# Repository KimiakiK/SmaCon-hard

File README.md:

# SmaCon-hard

# Features
- 

# Major Components
- STM32U575CIU6Q
Arm Cortex-M33 160MHz ROM 2MB RAM 786KB UFQFPN-48
- LCD
2.8inch 240x320 IPS ST7789 Touch GT911
- YMF825
FM音源
- 振動モータ
LD14-002

# Photos

# Parts List
- [STM32U575CIU6Q](https://mou.sr/46YhdRg)
- LCD (AliExpress)
- FM音源 YMF825 (AliExpress)
- [スピーカー](https://akizukidenshi.com/catalog/g/gP-12495/)
- [水晶振動子 12.228MHz](https://www.marutsu.co.jp/pc/i/1542722/)
- [3.5mmステレオミニジャック](https://www.marutsu.co.jp/pc/i/590750/)
- [EEPROM 1KB 25LC080C-E/MS](https://mou.sr/3XQXcYr)
- [振動モータ LD14-002](https://akizukidenshi.com/catalog/g/gP-06838/)
- [モータドライバ BD6211F](https://akizukidenshi.com/catalog/g/gI-05087/)
- [USB Type-Cコネクタ 5077CR-16SMC2-BK-TR](https://akizukidenshi.com/catalog/g/gC-14356/)
- [アナログジョイスティック JT8P-3.2T-B10K-1-16Y](https://akizukidenshi.com/catalog/g/gP-04048/)
- [タクトスイッチ(赤)](https://akizukidenshi.com/catalog/g/gP-03646/)
- [タクトスイッチ(黄)](https://akizukidenshi.com/catalog/g/gP-03650/)
- [タクトスイッチ(緑)](https://akizukidenshi.com/catalog/g/gP-03651/)
- [タクトスイッチ(青)](https://akizukidenshi.com/catalog/g/gP-03649/)
- [レバースイッチ TMHU27](https://akizukidenshi.com/catalog/g/gP-08071/)
- [リセットIC BD45285G 2.5V 50ms](https://www.marutsu.co.jp/pc/i/16146424/)
- [レギュレータ NJM2884U1-33 3.3V 500mA](https://akizukidenshi.com/catalog/g/gI-10673/)
- [ESD保護デバイス LXES11DAA2-137](https://akizukidenshi.com/catalog/g/gP-13816/)
- [フェライトビーズ BLM18PG600SH1](https://akizukidenshi.com/catalog/g/gP-04442/)
- [リセッタブルヒューズ 0.5A MF-NSMF050](https://akizukidenshi.com/catalog/g/gP-15300/)
- [NchパワーMOSFET AO3400A](https://akizukidenshi.com/catalog/g/gI-14653/)
- [FFCコネクタ 18pin 0.5mm](https://www.marutsu.co.jp/pc/i/2572902/)
- [FFCコネクタ 6pin 0.5mm](https://www.marutsu.co.jp/pc/i/2572910/)

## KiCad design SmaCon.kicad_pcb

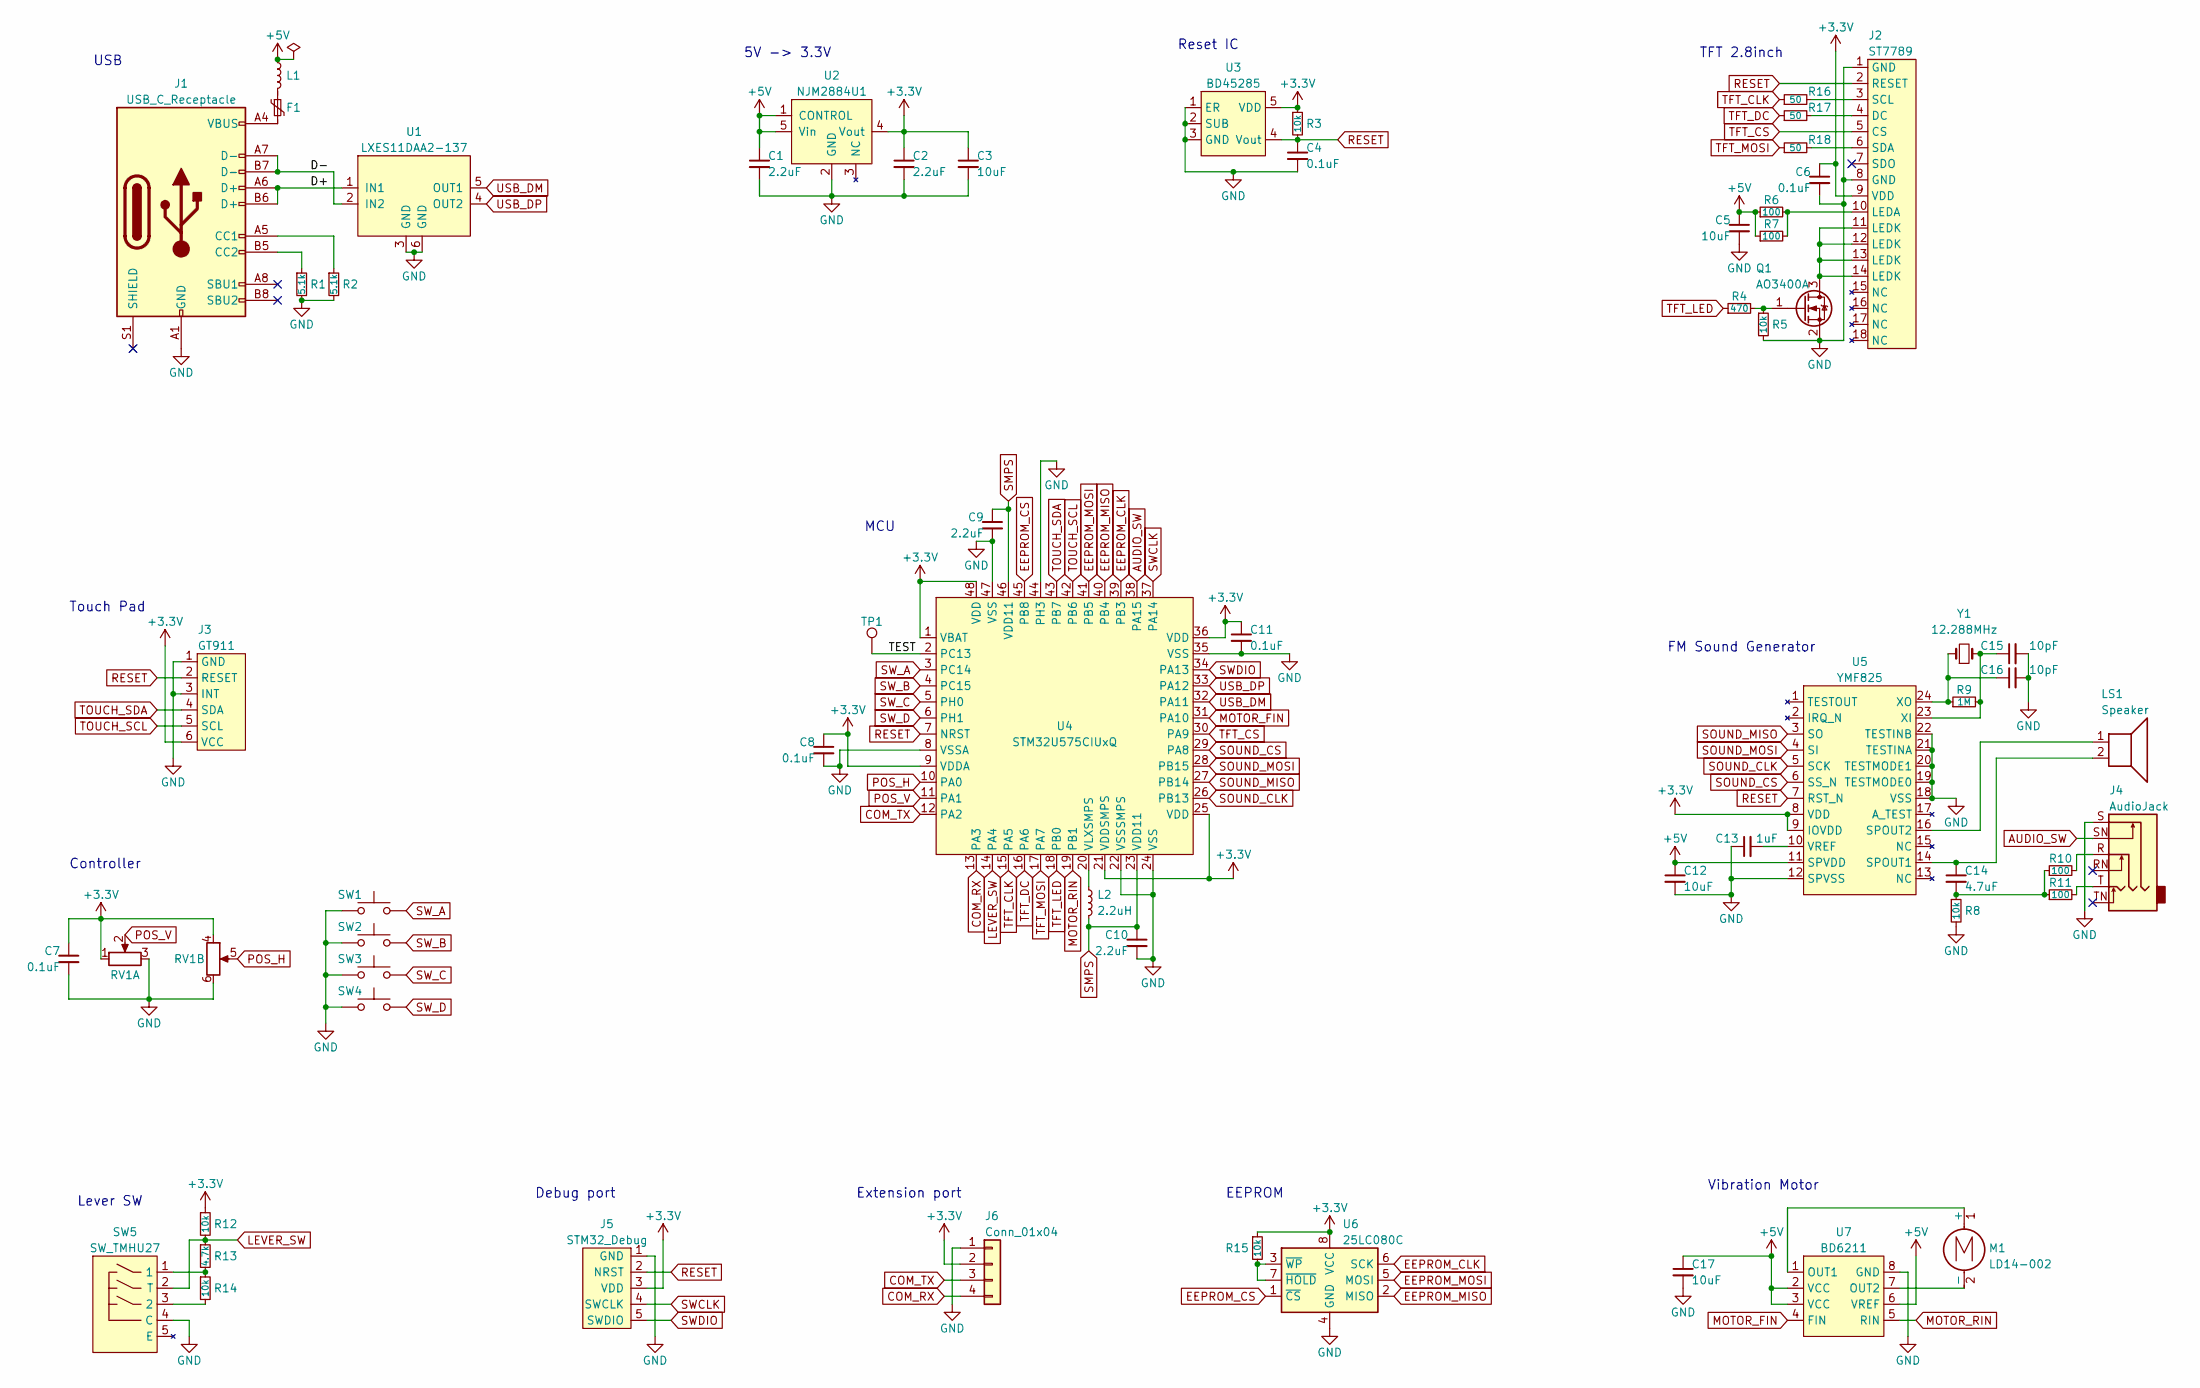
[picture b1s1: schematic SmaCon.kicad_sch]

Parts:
C1, C2, C9, C10: 2.2uF; 1005Metric
C3, C5, C12, C17: 10uF; 1608Metric
C4, C6, C7, C8, C11: 0.1uF; 1005Metric
C13: 1uF; 1005Metric
C14: 4.7uF; 1608Metric
C15, C16: 10pF; 1005Metric
F1: Polyfuse; 3216Metric
J1: USB_C_Receptacle; USB Type-C 5077CR-16SMC2-BK-TR
J2: ST7789; Hirose_FH12-18S-0.5SH_1x18-1MP_P0.50mm_Horizontal
J3: GT911; Hirose_FH12-6S-0.5SH_1x06-1MP_P0.50mm_Horizontal
J4: AudioJack; PJ-3420
J5: STM32_Debug; STM32_Debug_5pin
J6: Conn_01x04; PinHeader_1x04_P2.54mm_Horizontal
L1: L; 1608Metric
L2: 2.2uH; 2012Metric
LS1: Speaker; micro_speaker
M1: LD14-002
Q1: AO3400A; SOT-23
R1, R2: 5.1k; 1005Metric
R3, R5, R8, R12, R14, R15: 10k; 1005Metric
R4: 470; 1005Metric
R6, R7, R10, R11: 100; 2012Metric
R9: 1M; 1005Metric
R13: 4.7k; 1005Metric
R16, R17, R18: 50; 1005Metric
RV1: Potentiometer_Dual; JT8P-3.2T-B10K-1-16Y
SW1, SW2, SW3, SW4: SW_Push; tact_switch
SW5: SW_TMHU27
TP1: TestPoint; TestPoint_THTPad_D1.2mm_Drill0.8mm
U1: LXES11DAA2-137; LXES11D
U2: NJM2884U1; SOT-89-5
U3: BD45285; SOT-23-5
U4: STM32U575CIUxQ; QFN-48-1EP_7x7mm_P0.5mm_EP5.3x5.3mm
U5: YMF825; SSOP-24_5.3x8.2mm_P0.65mm
U6: 25LC080C; MSOP-8_3x3mm_P0.65mm
U7: BD6211; SOP-8_4.4x5.0mm_P1.27mm
Y1: 12.288MHz; Crystal_SMD_TXC_AX_8045-2Pin_8.0x4.5mm

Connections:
+3.3V: C2.1, C3.1, C6.1, C7.1, C8.1, C11.1, J2.9 (VDD), J3.6 (VCC), J5.3 (VDD), J6.2, R3.1, R12.1, R15.1, RV1.1, RV1.4, U2.4 (Vout), U3.5 (VDD), U4.1 (VBAT), U4.9 (VDDA), U4.21 (VDDSMPS), U4.25 (VDD), U4.36 (VDD), U4.48 (VDD), U5.8 (VDD), U5.9 (IOVDD), U6.8 (VCC)
+5V: C1.1, C5.1, C12.1, C17.1, L1.1, R6.1, R7.1, U2.1 (CONTROL), U2.5 (Vin), U5.11 (SPVDD), U7.2 (VCC), U7.3 (VCC), U7.6 (VREF)
/D+: J1.A6 (D+), J1.B6 (D+), U1.1 (IN1)
/D-: J1.A7 (D-), J1.B7 (D-), U1.2 (IN2)
/TEST: TP1.1, U4.2 (PC13)
AUDIO_SW: J4.SN, U4.38 (PA15)
COM_RX: J6.4, U4.13 (PA3)
COM_TX: J6.3, U4.12 (PA2)
EEPROM_CLK: U4.39 (PB3), U6.6 (SCK)
EEPROM_CS: U4.45 (PB8), U6.1 (~CS)
EEPROM_MISO: U4.40 (PB4), U6.2 (MISO)
EEPROM_MOSI: U4.41 (PB5), U6.5 (MOSI)
GND: C1.2, C2.2, C3.2, C4.2, C5.2, C6.2, C7.2, C8.2, C9.2, C10.2, C11.2, C12.2, C13.1, C15.2, C16.2, C17.2, J1.A1 (GND), J1.A12 (GND), J1.B1 (GND), J1.B12 (GND), J2.1 (GND), J2.8 (GND), J3.1 (GND), J3.3 (INT), J4.S, J5.1 (GND), J6.1, Q1.2 (S), R1.2, R2.2, R5.2, R8.2, RV1.3, RV1.6, SW1.1, SW2.1, SW3.1, SW4.1, SW5.4 (C), U1.3 (GND), U1.6 (GND), U2.2 (GND), U3.1 (ER), U3.2 (SUB), U3.3 (GND), U4.8 (VSSA), U4.22 (VSSSMPS), U4.24 (VSS), U4.35 (VSS), U4.44 (PH3), U4.47 (VSS), U5.12 (SPVSS), U5.18 (VSS), U5.19 (TESTMODE0), U5.20 (TESTMODE1), U5.21 (TESTINA), U5.22 (TESTINB), U6.4 (GND), U7.8 (GND)
LEVER_SW: R12.2, R13.1, SW5.2 (T), U4.14 (PA4)
MOTOR_FIN: U4.31 (PA10), U7.4 (FIN)
MOTOR_RIN: U4.19 (PB1), U7.5 (RIN)
unnamed: C14.2, R8.1, R10.1, R11.1
unnamed: F1.1, L1.2
unnamed: F1.2, J1.A4 (VBUS), J1.A9 (VBUS), J1.B4 (VBUS), J1.B9 (VBUS)
unnamed: J1.A5 (CC1), R2.1
unnamed: J1.B5 (CC2), R1.1
unnamed: J2.4 (DC), R17.2
unnamed: J2.10 (LEDA), R6.2, R7.2
unnamed: J2.3 (SCL), R16.2
unnamed: J2.6 (SDA), R18.2
unnamed: J4.R, R10.2
unnamed: J4.T, R11.2
unnamed: M1.1 (+), U7.1 (OUT1)
unnamed: M1.2 (-), U7.7 (OUT2)
unnamed: J2.11 (LEDK), J2.12 (LEDK), J2.13 (LEDK), J2.14 (LEDK), Q1.3 (D)
unnamed: Q1.1 (G), R4.2, R5.1
unnamed: R13.2, R14.1, SW5.1
unnamed: R14.2, SW5.3 (2)
unnamed: L2.1, U4.20 (VLXSMPS)
unnamed: C14.1, LS1.2, U5.14 (SPOUT1)
unnamed: LS1.1, U5.16 (SPOUT2)
unnamed: C13.2, U5.10 (VREF)
unnamed: C15.1, R9.2, U5.23 (XI), Y1.2
unnamed: C16.1, R9.1, U5.24 (XO), Y1.1
unnamed: R15.2, U6.3 (~WP), U6.7 (~HOLD)
POS_H: RV1.5, U4.10 (PA0)
POS_V: RV1.2, U4.11 (PA1)
RESET: C4.1, J2.2 (RESET), J3.2 (RESET), J5.2 (NRST), R3.2, U3.4 (Vout), U4.7 (NRST), U5.7 (RST_N)
SMPS: C9.1, C10.1, L2.2, U4.23 (VDD11), U4.46 (VDD11)
SOUND_CLK: U4.26 (PB13), U5.5 (SCK)
SOUND_CS: U4.29 (PA8), U5.6 (SS_N)
SOUND_MISO: U4.27 (PB14), U5.3 (SO)
SOUND_MOSI: U4.28 (PB15), U5.4 (SI)
SWCLK: J5.4 (SWCLK), U4.37 (PA14)
SWDIO: J5.5 (SWDIO), U4.34 (PA13)
SW_A: SW1.2, U4.3 (PC14)
SW_B: SW2.2, U4.4 (PC15)
SW_C: SW3.2, U4.5 (PH0)
SW_D: SW4.2, U4.6 (PH1)
TFT_CLK: R16.1, U4.15 (PA5)
TFT_CS: J2.5 (CS), U4.30 (PA9)
TFT_DC: R17.1, U4.16 (PA6)
TFT_LED: R4.1, U4.18 (PB0)
TFT_MOSI: R18.1, U4.17 (PA7)
TOUCH_SCL: J3.5 (SCL), U4.42 (PB6)
TOUCH_SDA: J3.4 (SDA), U4.43 (PB7)
USB_DM: U1.5 (OUT1), U4.32 (PA11)
USB_DP: U1.4 (OUT2), U4.33 (PA12)

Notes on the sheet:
Controller
Reset IC
Extension port
Vibration Motor
USB
EEPROM
Touch Pad
Lever SW
FM Sound Generator
Debug port
TFT 2.8inch
5V -> 3.3V
MCU

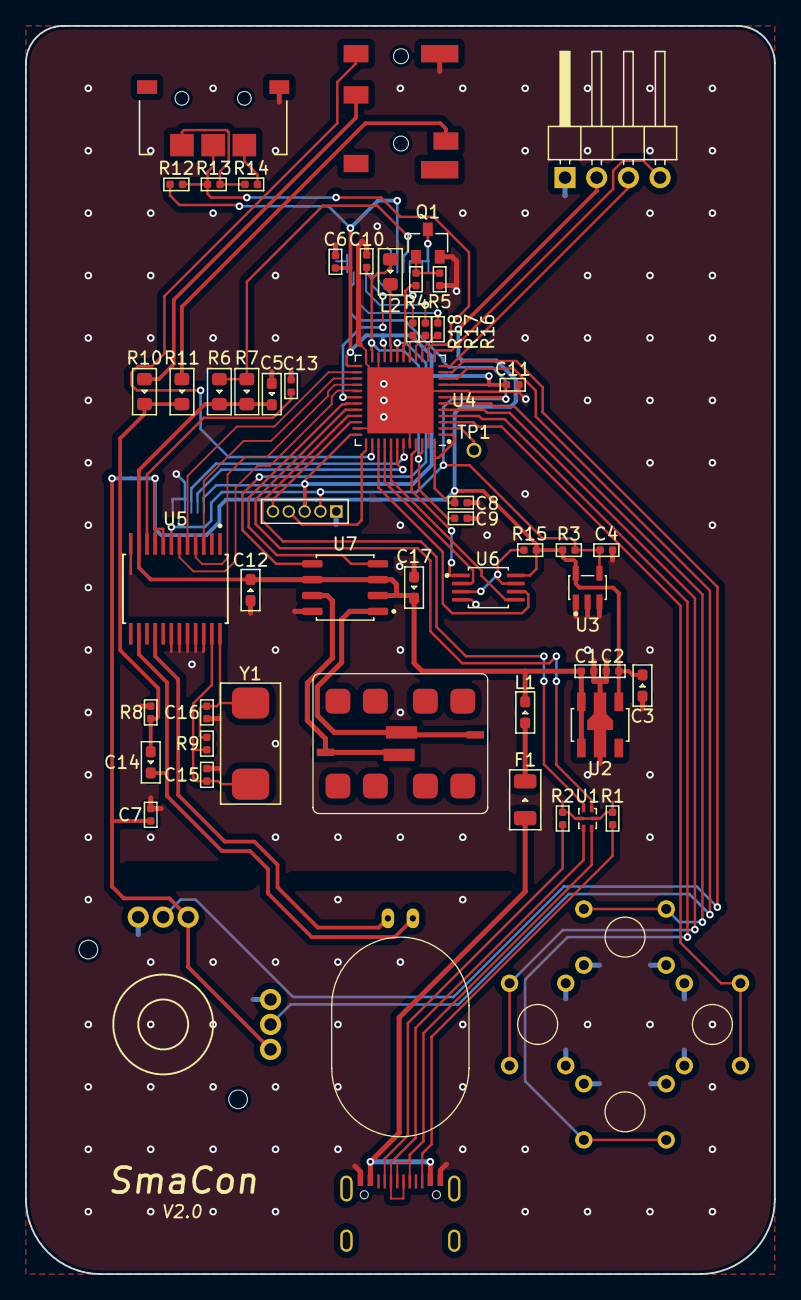
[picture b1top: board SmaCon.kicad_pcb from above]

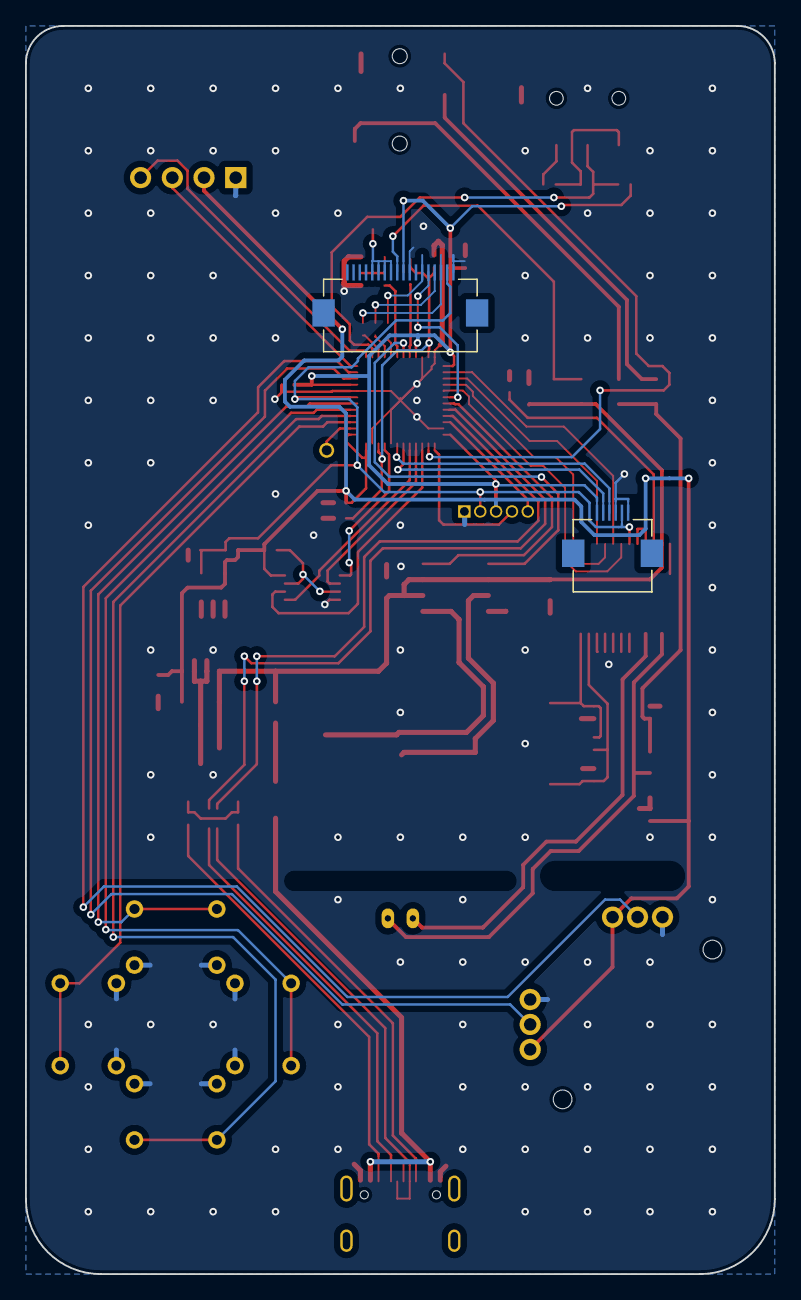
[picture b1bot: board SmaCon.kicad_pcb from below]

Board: 2 copper layers, 60.0 x 100.0 mm, 64 parts (2 on the bottom side), 63 nets.

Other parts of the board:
1, 2: 22b1b73a-550e-4fe2-9098-770367972fd8

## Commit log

2023-02-12 プロジェクト作成
2023-07-13 回路図作成
2023-07-13 EEPROMに変更、マイコン型番変更
2023-07-19 部品選定
2023-07-25 基板 V1.0
2023-08-05 基板 V1.1
2023-08-21 基板 V1.2
2023-09-14 基板 V2.0
